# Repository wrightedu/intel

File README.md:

# Welcome!

## Today we are meeting in: 152C Russ for our FINAL DAY!!!

Great job on your designs all!  We will recume fabrication after lunch if anyone has any loose ends to tie up on their boards.

Resources:

* This site: [**github.com/wrightedu/intel**](github.com/wrightedu/intel)
  * [`./arduino-src/`](arduino-src/README.md) : arduino source files will be put here
  * [`./KiCad/`](KiCad/README.md) : KiCad example project files (mostly starter templates)
  * More folders and files will be added as we go through the course

* Download and install Arduino IDE from here: https://www.arduino.cc/en/software
* Download and install KiCAD from here: https://www.kicad.org/download/
* CSE Department Discord server: [https://discord.gg/pMUMzTt](https://discord.gg/pMUMzTt)
  * `#other-roles` and click on `Intel Summer Camp`

---

# The Format

* `*.md` a markdown formatted file for pretty web rendering here
* PowerPoint (`*.pptx`) and `*.pdf` files (self explanatory)
* `*.ino` files are for the arduino

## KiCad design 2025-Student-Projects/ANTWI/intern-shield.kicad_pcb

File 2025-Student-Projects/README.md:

# 2025 Student Projects

This folder contains the projects developed by the 20205 Intel Interns at Wright State University.

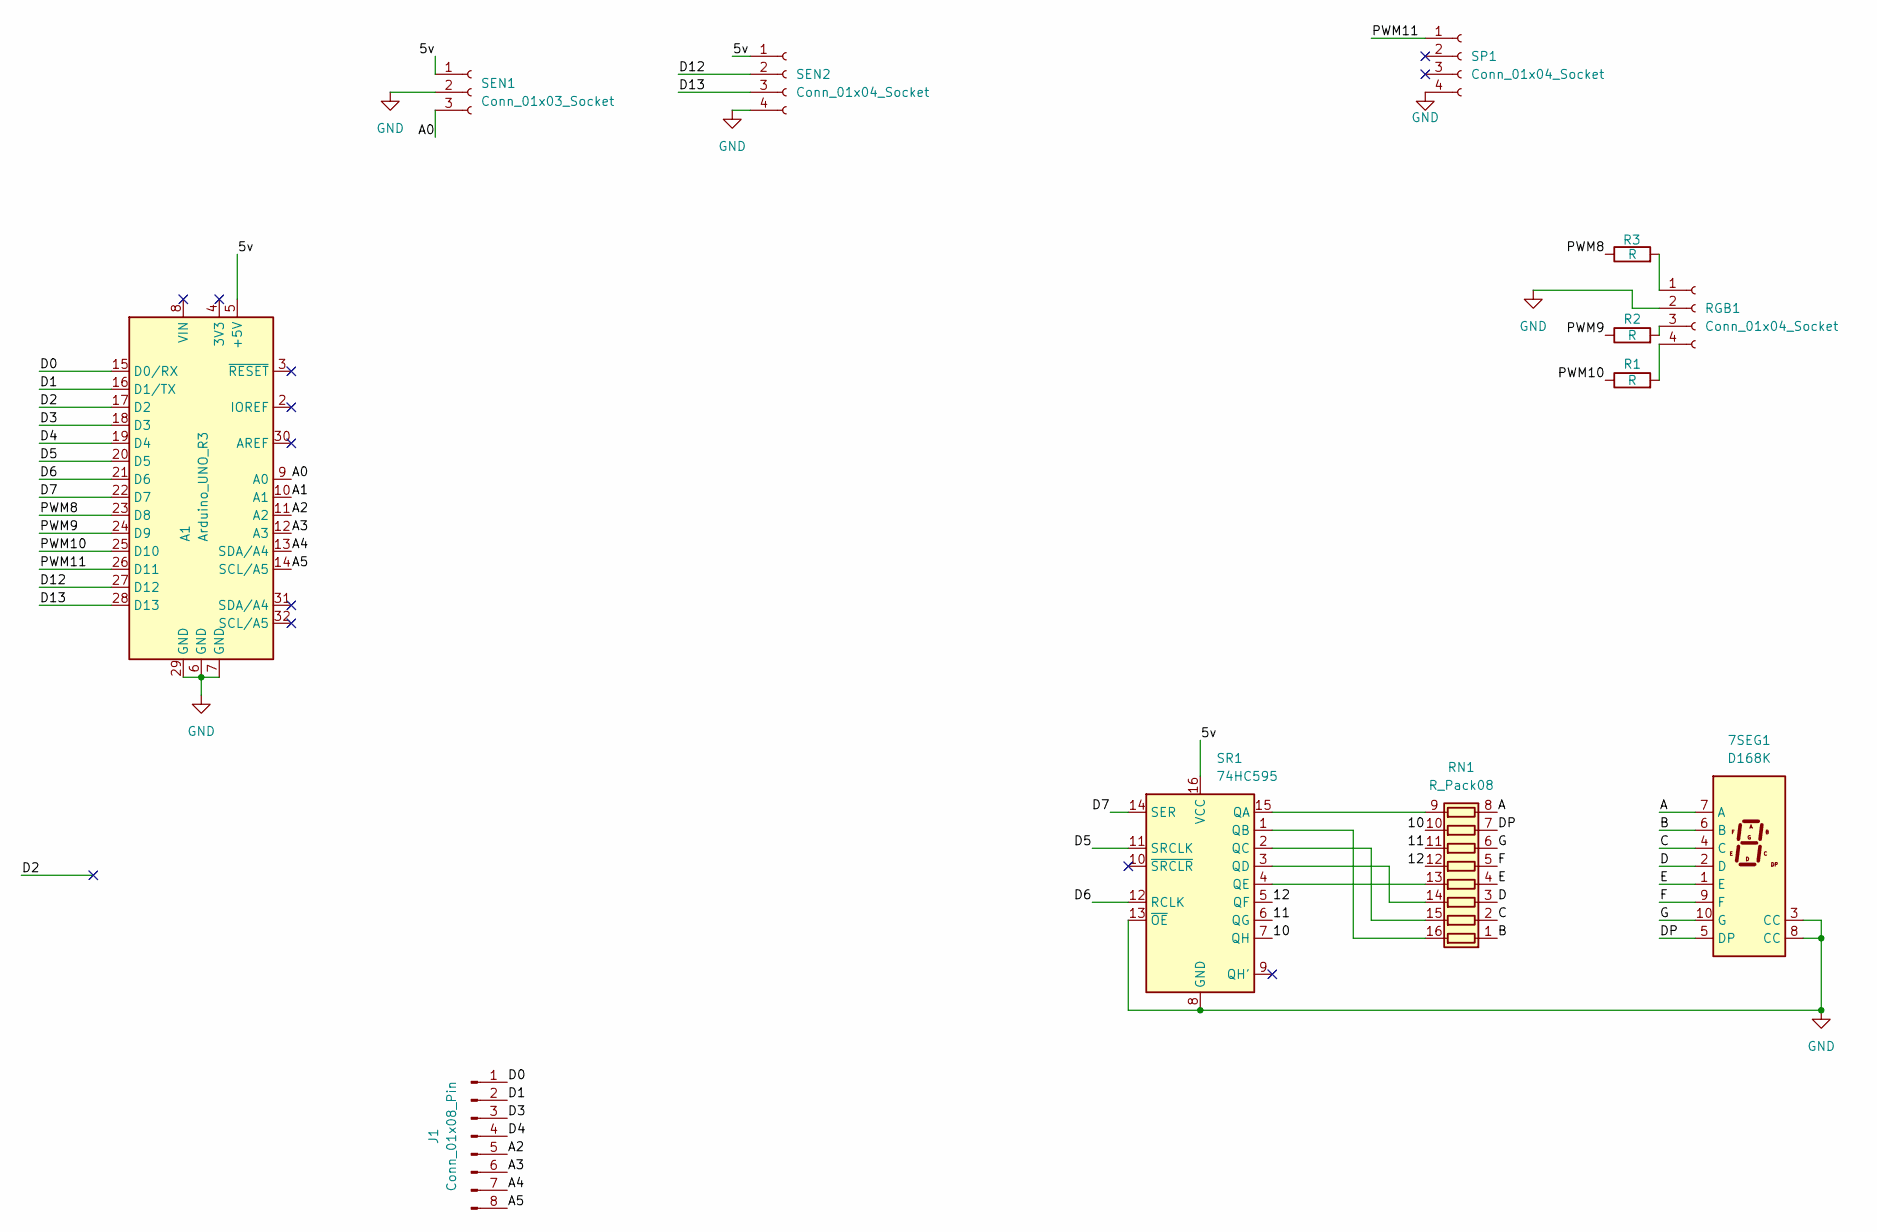
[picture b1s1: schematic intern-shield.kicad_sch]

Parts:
7SEG1: D168K; LS-5161AS
A1: Arduino_UNO_R3
J1: Conn_01x08_Pin; PinHeader_1x08_P2.54mm_Vertical
R1, R2, R3: R; R_Axial_DIN0207_L6.3mm_D2.5mm_P7.62mm_Horizontal
RGB1: Conn_01x04_Socket; PinSocket_1x04_P2.54mm_Vertical
RN1: R_Pack08; DIP-16_W7.62mm_Socket
SEN1: Conn_01x03_Socket; PinSocket_1x03_P2.54mm_Vertical
SEN2: Conn_01x04_Socket; PinSocket_1x04_P2.54mm_Vertical
SP1: Conn_01x04_Socket; PinSocket_1x04_P2.54mm_Vertical
SR1: 74HC595; DIP-16_W7.62mm_Socket

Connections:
/5v: A1.5 (+5V), SEN1.1, SEN2.1, SR1.16 (VCC)
/10: RN1.10 (R7.2), SR1.7 (QH)
/11: RN1.11 (R6.2), SR1.6 (QG)
/12: RN1.12 (R5.2), SR1.5 (QF)
/A: 7SEG1.7 (A), RN1.8 (R8.1)
/A0: A1.9 (A0), SEN1.3
/A1: A1.10 (A1)
/A2: A1.11 (A2), J1.5
/A3: A1.12 (A3), J1.6
/A4: A1.13 (SDA/A4), J1.7
/A5: A1.14 (SCL/A5), J1.8
/B: 7SEG1.6 (B), RN1.1 (R1.1)
/C: 7SEG1.4 (C), RN1.2 (R2.1)
/D: 7SEG1.2 (D), RN1.3 (R3.1)
/D0: A1.15 (D0/RX), J1.1
/D1: A1.16 (D1/TX), J1.2
/D2: A1.17 (D2)
/D3: A1.18 (D3), J1.3
/D4: A1.19 (D4), J1.4
/D5: A1.20 (D5), SR1.11 (SRCLK)
/D6: A1.21 (D6), SR1.12 (RCLK)
/D7: A1.22 (D7), SR1.14 (SER)
/D12: A1.27 (D12), SEN2.2
/D13: A1.28 (D13), SEN2.3
/DP: 7SEG1.5 (DP), RN1.7 (R7.1)
/E: 7SEG1.1 (E), RN1.4 (R4.1)
/F: 7SEG1.9 (F), RN1.5 (R5.1)
/G: 7SEG1.10 (G), RN1.6 (R6.1)
/PWM8: A1.23 (D8), R3.1
/PWM9: A1.24 (D9), R2.1
/PWM10: A1.25 (D10), R1.1
/PWM11: A1.26 (D11), SP1.1
GND: 7SEG1.3 (CC), 7SEG1.8 (CC), A1.6 (GND), A1.7 (GND), A1.29 (GND), RGB1.2, SEN1.2, SEN2.4, SP1.4, SR1.8 (GND), SR1.13 (~OE)
unnamed: R3.2, RGB1.1
unnamed: R2.2, RGB1.3
unnamed: R1.2, RGB1.4
unnamed: RN1.16 (R1.2), SR1.1 (QB)
unnamed: RN1.15 (R2.2), SR1.2 (QC)
unnamed: RN1.14 (R3.2), SR1.3 (QD)
unnamed: RN1.13 (R4.2), SR1.4 (QE)
unnamed: RN1.9 (R8.2), SR1.15 (QA)

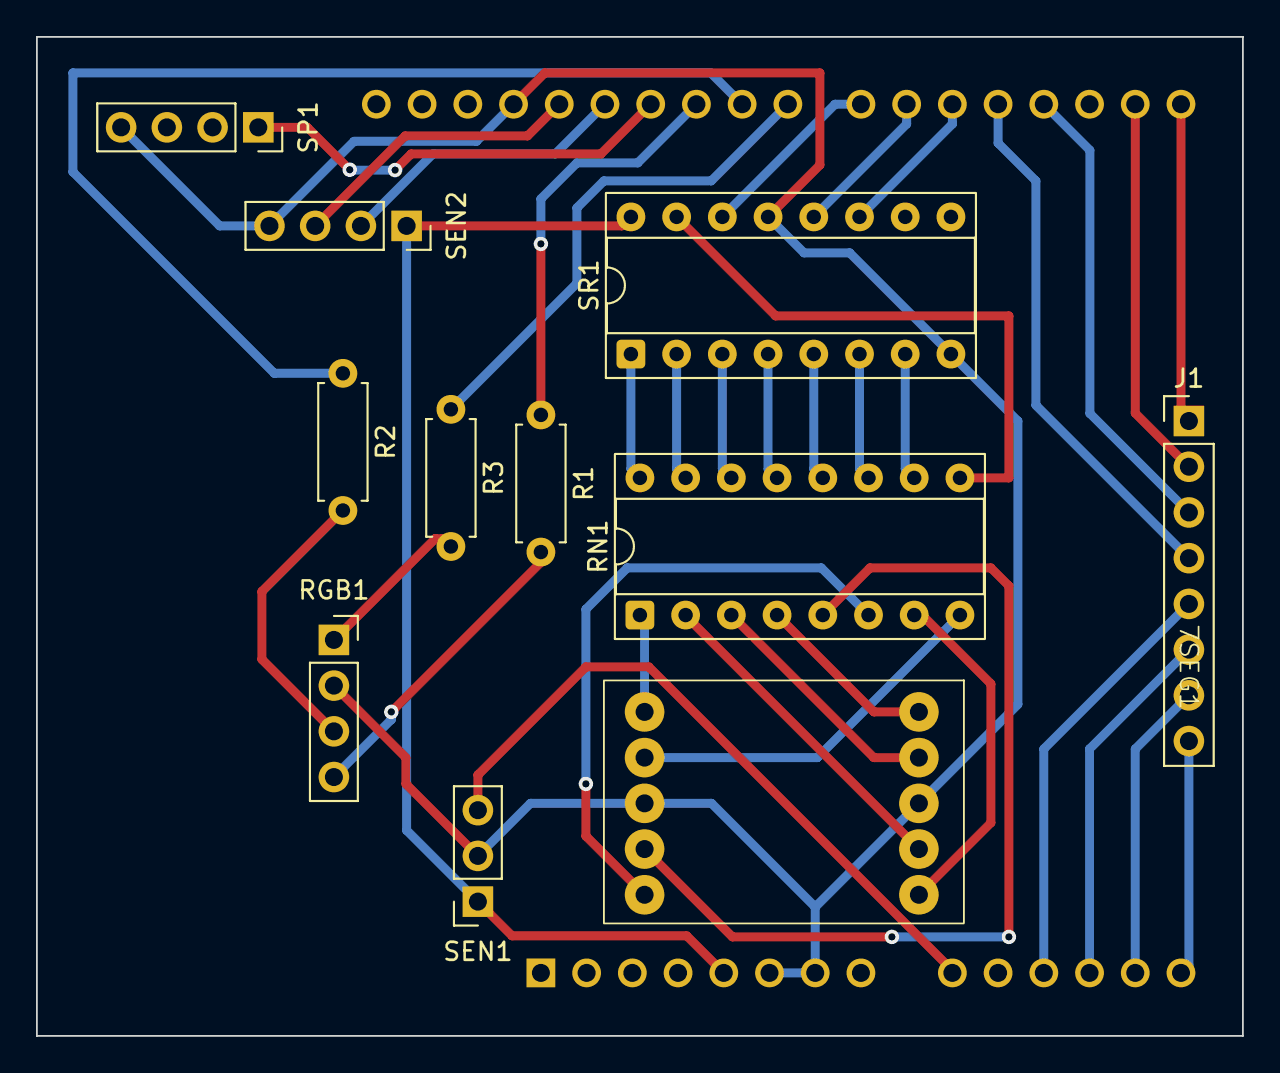
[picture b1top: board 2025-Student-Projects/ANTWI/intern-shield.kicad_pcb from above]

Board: 2 copper layers, 67.0 x 55.5 mm, 12 parts (1 on the bottom side), 39 nets.

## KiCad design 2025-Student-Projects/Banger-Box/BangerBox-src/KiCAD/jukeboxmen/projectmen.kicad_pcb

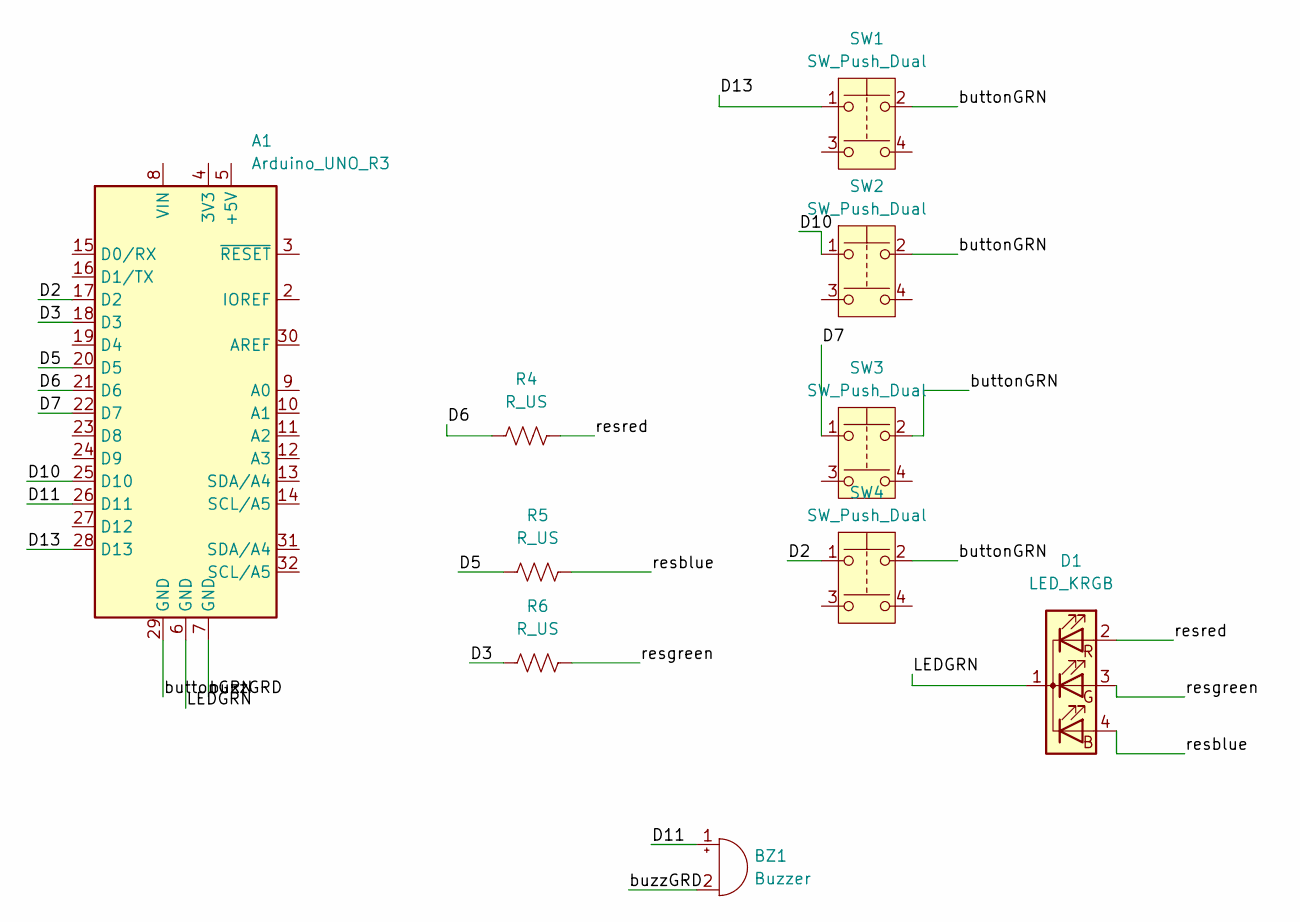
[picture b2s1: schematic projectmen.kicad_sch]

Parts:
A1: Arduino_UNO_R3
BZ1: Buzzer; Buzzer_12x9.5RM7.6
D1: LED_KRGB; LED_D5.0mm-4_RGB
R4, R5, R6: R_US; R_Axial_DIN0207_L6.3mm_D2.5mm_P10.16mm_Horizontal
SW1, SW2, SW3, SW4: SW_Push_Dual; SW_PUSH_6mm_H4.3mm

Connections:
/D2: A1.17 (D2), SW4.1
/D3: A1.18 (D3), R6.1
/D5: A1.20 (D5), R5.1
/D6: A1.21 (D6), R4.1
/D7: A1.22 (D7), SW3.1
/D10: A1.25 (D10), SW2.1
/D11: A1.26 (D11), BZ1.1 (+)
/D13: A1.28 (D13), SW1.1
/LEDGRN: A1.6 (GND), D1.1 (K)
/buttonGRN: A1.29 (GND), SW1.2, SW2.2, SW3.2, SW4.2
/buzzGRD: A1.7 (GND), BZ1.2 (-)
/resblue: D1.4 (BA), R5.2
/resgreen: D1.3 (GA), R6.2
/resred: D1.2 (RA), R4.2

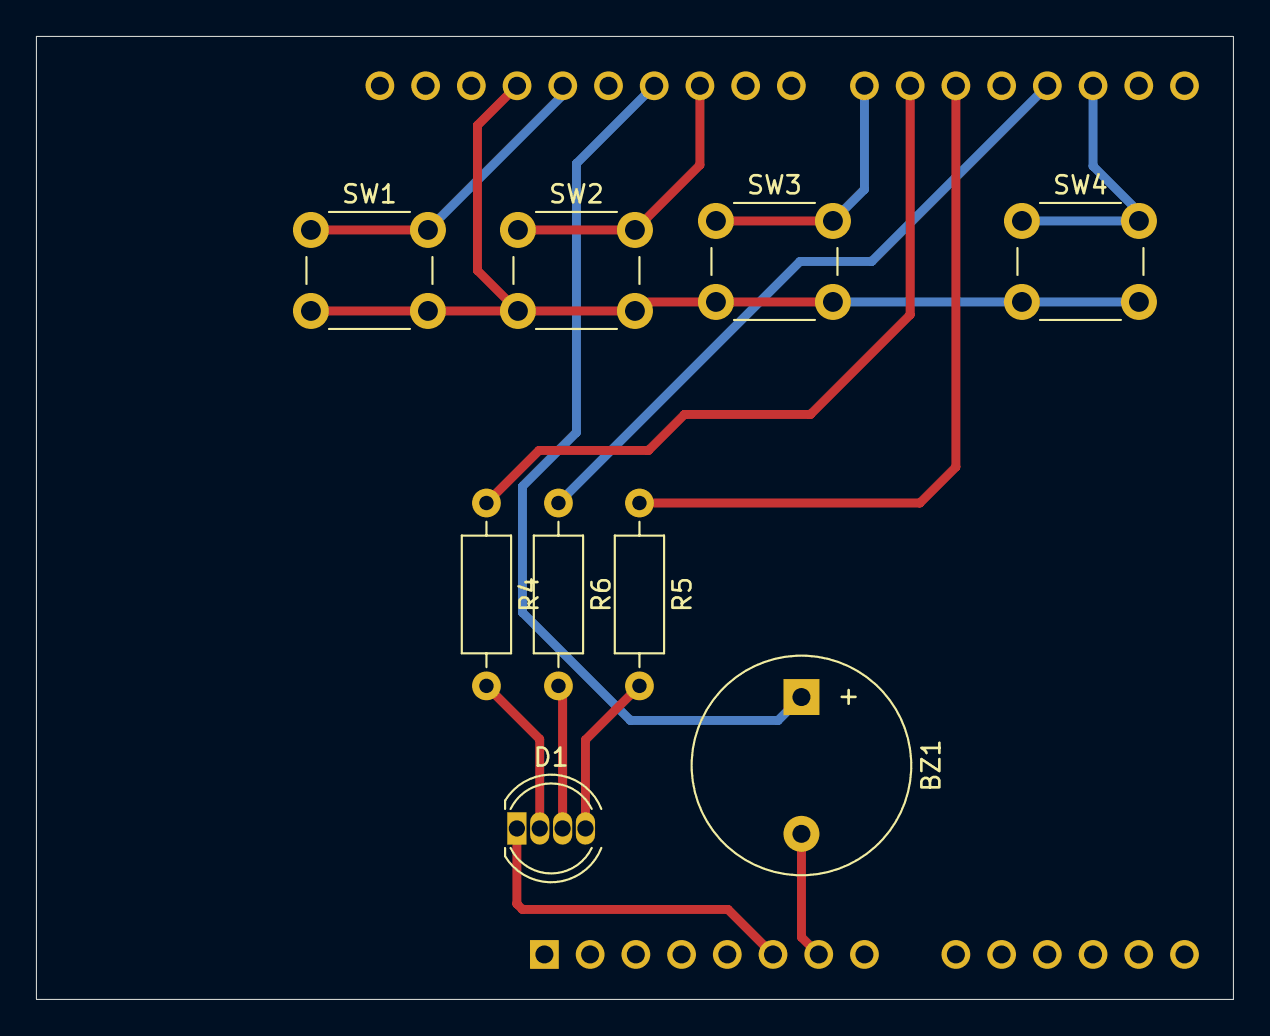
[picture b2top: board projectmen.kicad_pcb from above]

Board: 2 copper layers, 66.5 x 53.5 mm, 10 parts (1 on the bottom side), 14 nets.

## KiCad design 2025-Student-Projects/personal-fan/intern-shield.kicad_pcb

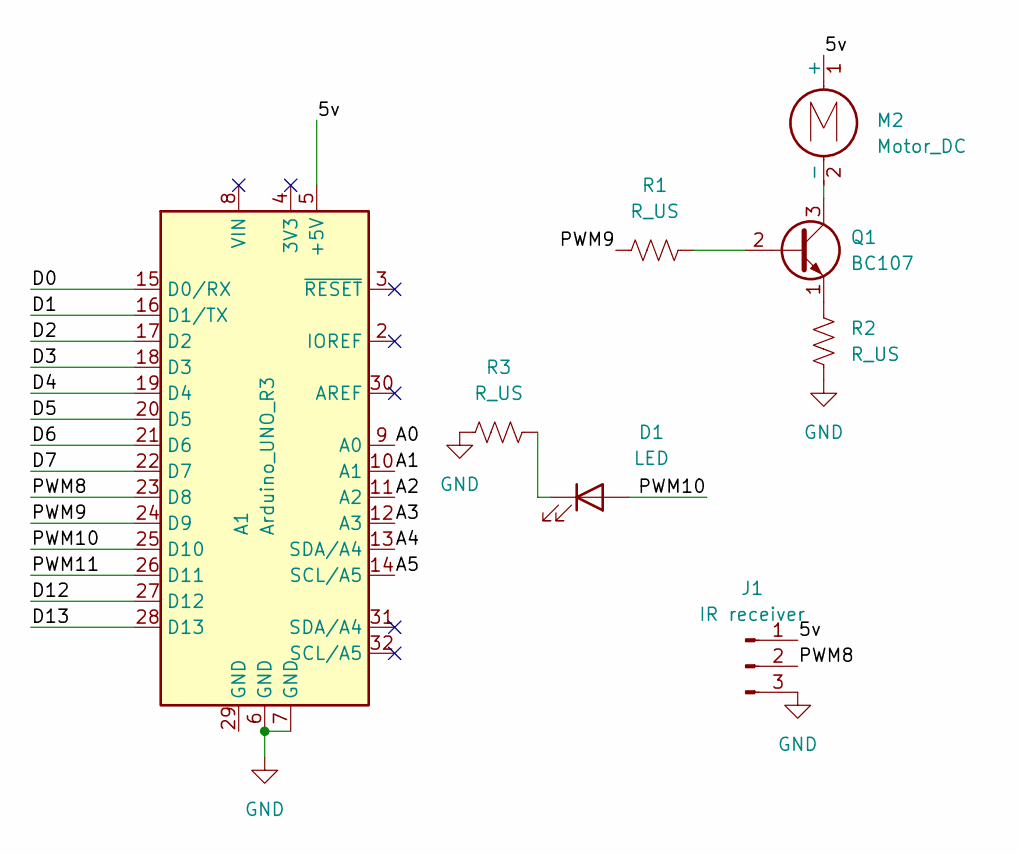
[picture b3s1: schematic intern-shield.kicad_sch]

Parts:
A1: Arduino_UNO_R3
D1: LED; LED_D3.0mm_Horizontal_O3.81mm_Z2.0mm
J1: IR receiver; PinHeader_1x03_P2.54mm_Vertical
M2: Motor_DC; PinHeader_1x02_P2.54mm_Vertical
Q1: BC107; TO-18-3
R1, R2, R3: R_US; R_Axial_DIN0207_L6.3mm_D2.5mm_P10.16mm_Horizontal

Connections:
/5v: A1.5 (+5V), J1.1, M2.1 (+)
/A0: A1.9 (A0)
/A1: A1.10 (A1)
/A2: A1.11 (A2)
/A3: A1.12 (A3)
/A4: A1.13 (SDA/A4)
/A5: A1.14 (SCL/A5)
/D0: A1.15 (D0/RX)
/D1: A1.16 (D1/TX)
/D2: A1.17 (D2)
/D3: A1.18 (D3)
/D4: A1.19 (D4)
/D5: A1.20 (D5)
/D6: A1.21 (D6)
/D7: A1.22 (D7)
/D12: A1.27 (D12)
/D13: A1.28 (D13)
/PWM8: A1.23 (D8), J1.2
/PWM9: A1.24 (D9), R1.1
/PWM10: A1.25 (D10), D1.2 (A)
/PWM11: A1.26 (D11)
GND: A1.6 (GND), A1.7 (GND), J1.3, R2.1, R3.1
unnamed: D1.1 (K), R3.2
unnamed: M2.2 (-), Q1.3 (C)
unnamed: Q1.2 (B), R1.2
unnamed: Q1.1 (E), R2.2

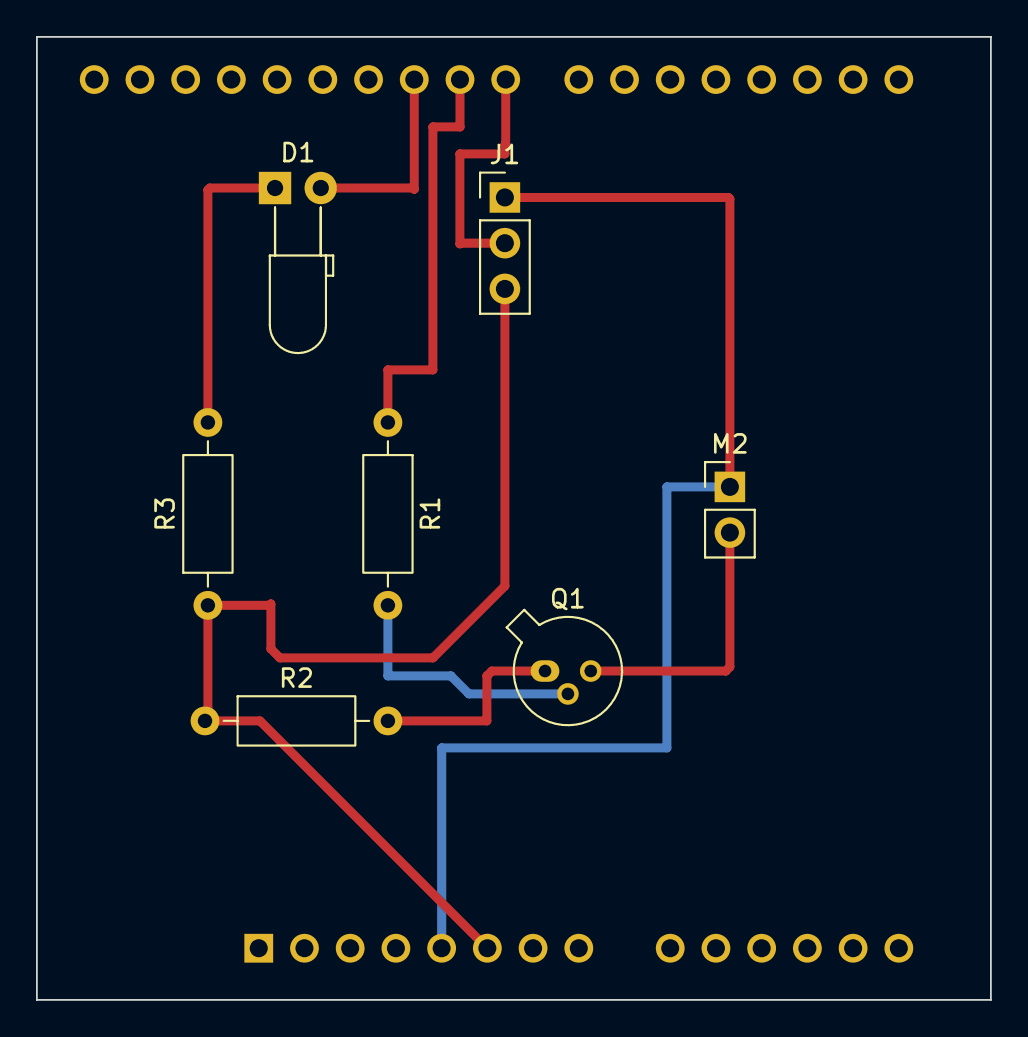
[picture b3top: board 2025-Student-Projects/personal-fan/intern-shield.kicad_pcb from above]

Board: 2 copper layers, 53.0 x 53.5 mm, 8 parts (1 on the bottom side), 9 nets.

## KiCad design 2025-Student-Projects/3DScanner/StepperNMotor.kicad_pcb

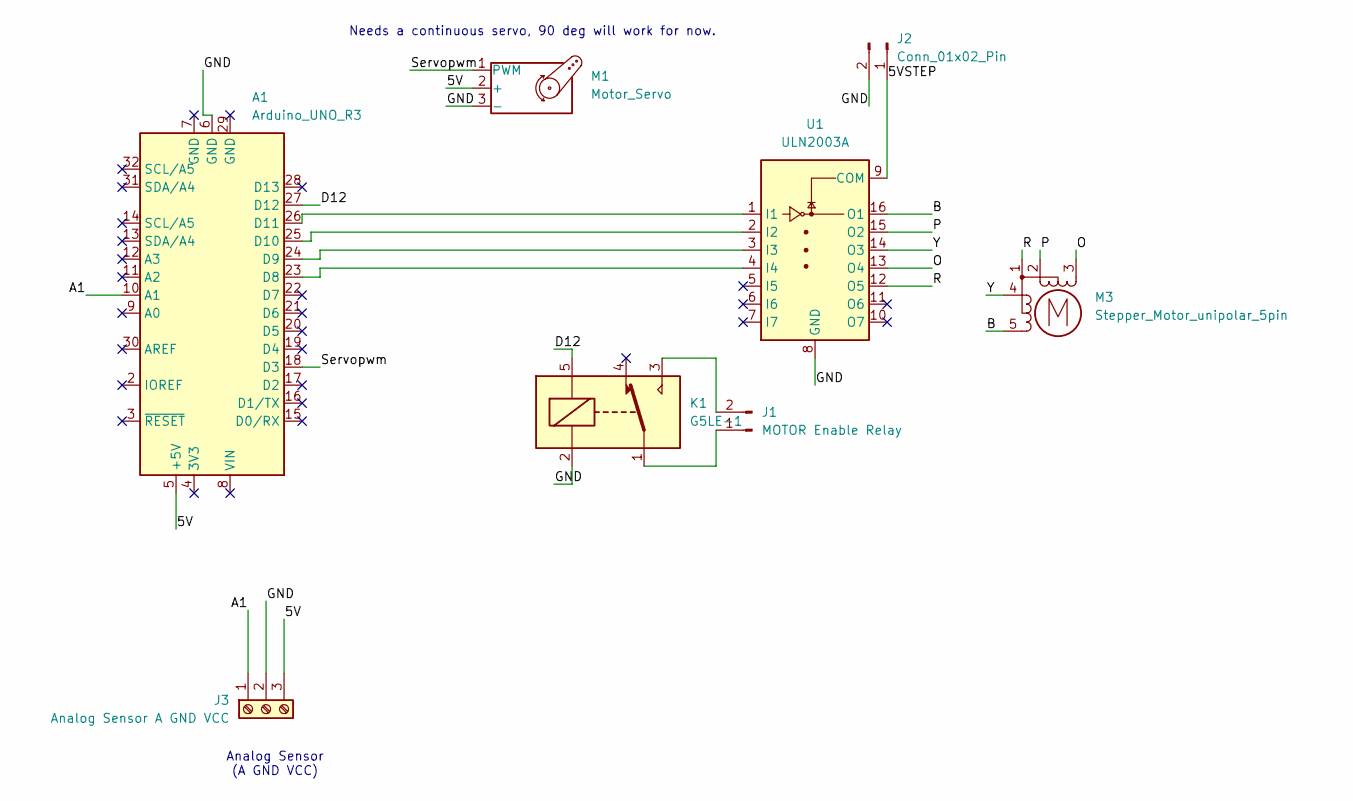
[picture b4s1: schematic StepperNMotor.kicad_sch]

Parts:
A1: Arduino_UNO_R3
J1: MOTOR Enable Relay; AMASS_XT30U-F_1x02_P5.0mm_Vertical
J2: Conn_01x02_Pin; PinSocket_1x02_P2.54mm_Vertical
J3: Analog Sensor A GND VCC; TerminalBlock_MetzConnect_Type055_RT01503HDWU_1x03_P5.00mm_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
K1: G5LE-1; Relay_SPDT_Omron-G5LE-1
M1: Motor_Servo; PinSocket_1x03_P2.54mm_Vertical
M3: Stepper_Motor_unipolar_5pin; PinHeader_1x05_P2.54mm_Vertical
U1: ULN2003A; DIP-16_W7.62mm

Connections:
/5V: A1.5 (+5V), J3.3, M1.2 (+)
/5VSTEP: J2.1, U1.9 (COM)
/A1: A1.10 (A1), J3.1
/B: M3.5, U1.16 (O1)
/D12: A1.27 (D12), K1.5
/GND: A1.6 (GND), J2.2, J3.2, K1.2, M1.3 (-), U1.8 (GND)
/O: M3.3 (-), U1.13 (O4)
/P: M3.2, U1.15 (O2)
/R: M3.1, U1.12 (O5)
/Servopwm: A1.18 (D3), M1.1 (PWM)
/Y: M3.4, U1.14 (O3)
unnamed: A1.23 (D8), U1.4 (I4)
unnamed: A1.24 (D9), U1.3 (I3)
unnamed: A1.25 (D10), U1.2 (I2)
unnamed: A1.26 (D11), U1.1 (I1)
unnamed: J1.1, K1.1
unnamed: J1.2, K1.3

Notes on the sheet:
Needs a continuous servo, 90 deg will work for now.
Analog Sensor (A GND VCC)

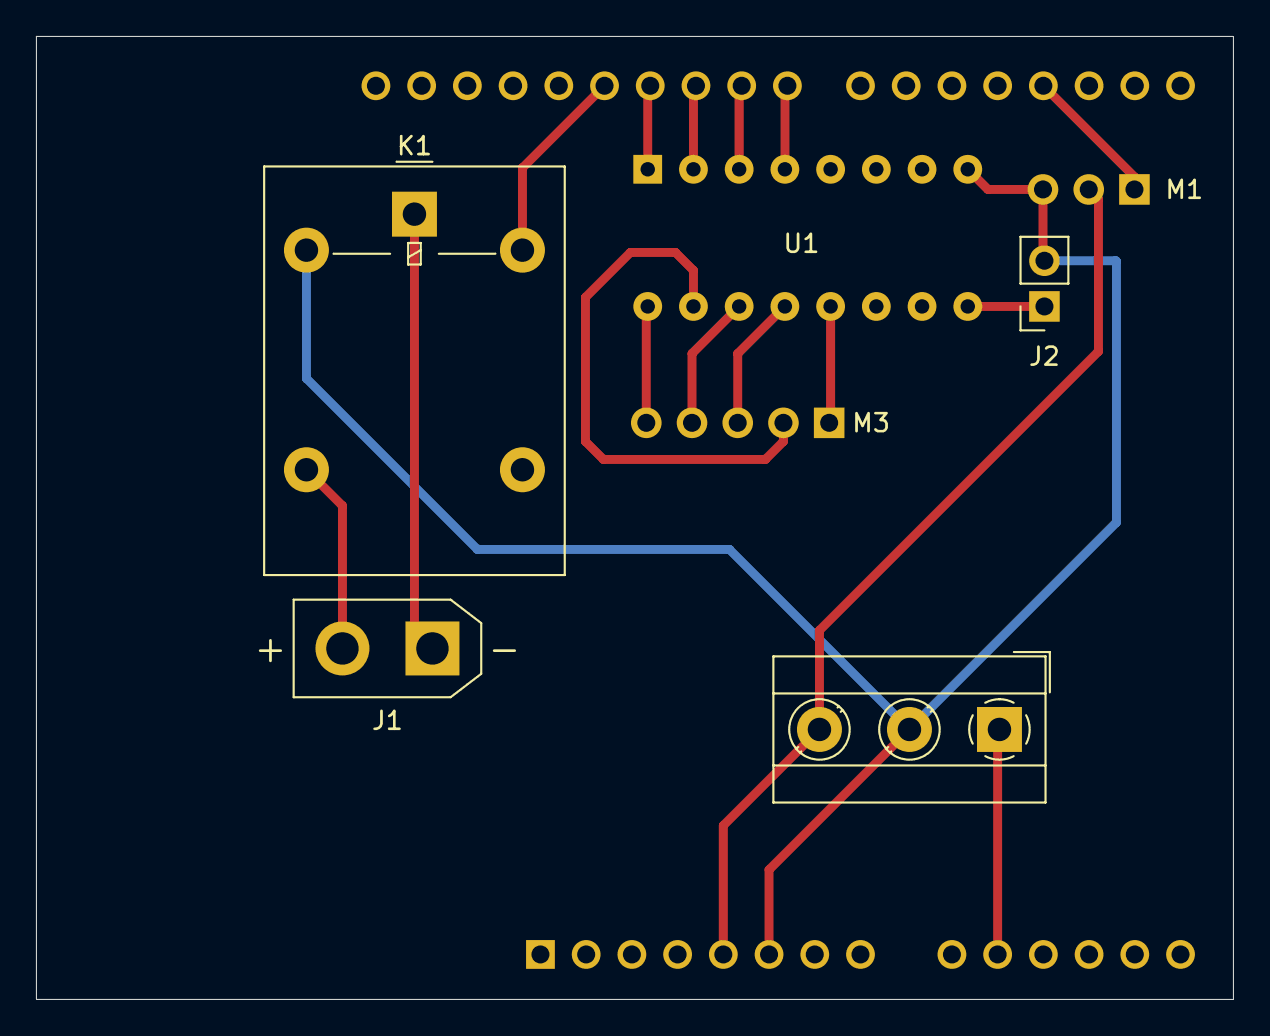
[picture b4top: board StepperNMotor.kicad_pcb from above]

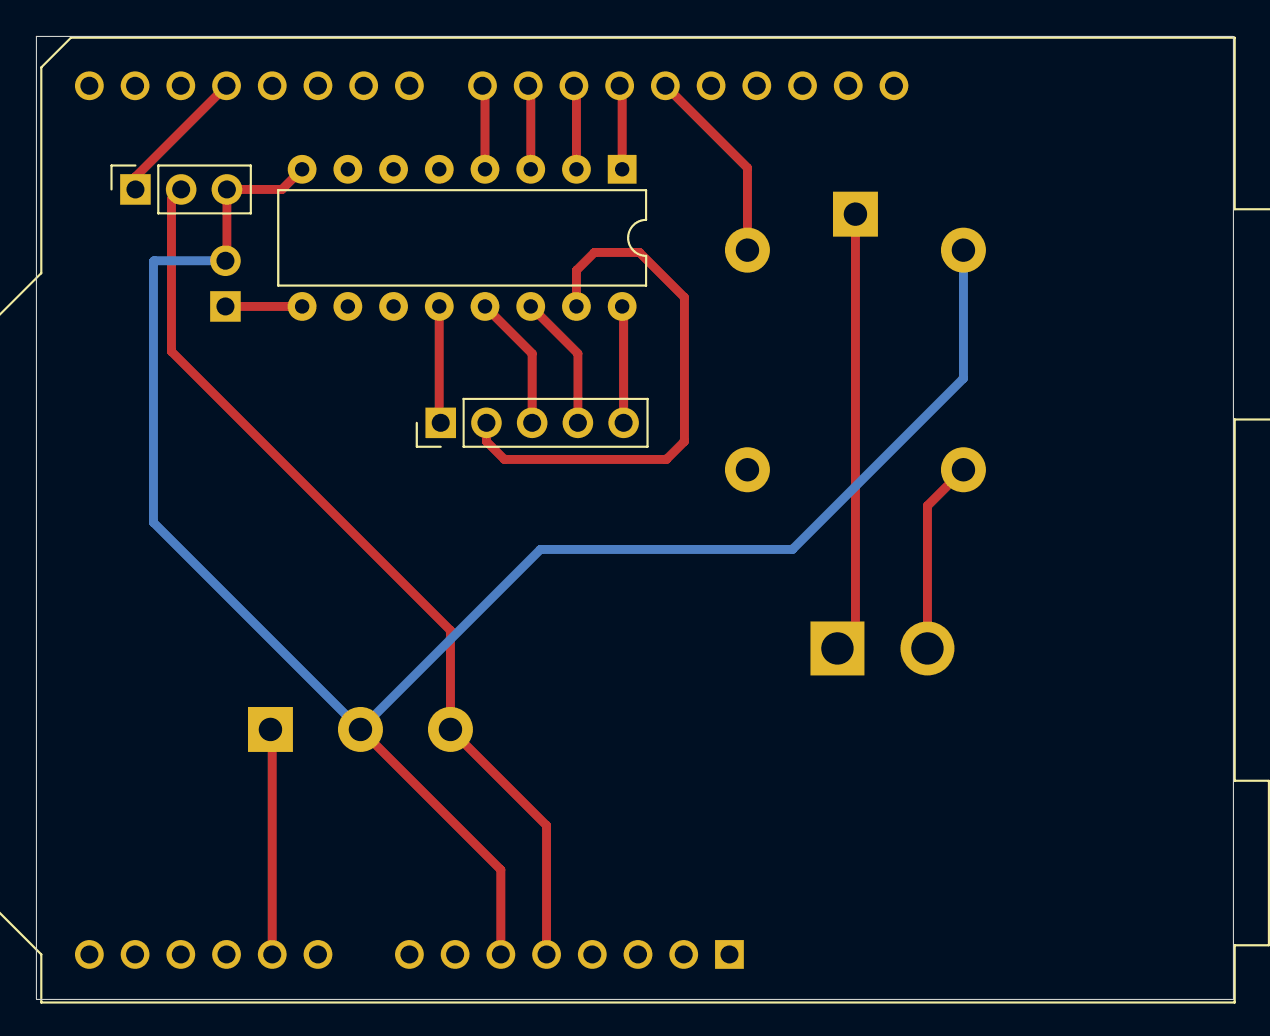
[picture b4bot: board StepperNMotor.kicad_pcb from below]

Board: 2 copper layers, 66.5 x 53.5 mm, 8 parts (4 on the bottom side), 17 nets.

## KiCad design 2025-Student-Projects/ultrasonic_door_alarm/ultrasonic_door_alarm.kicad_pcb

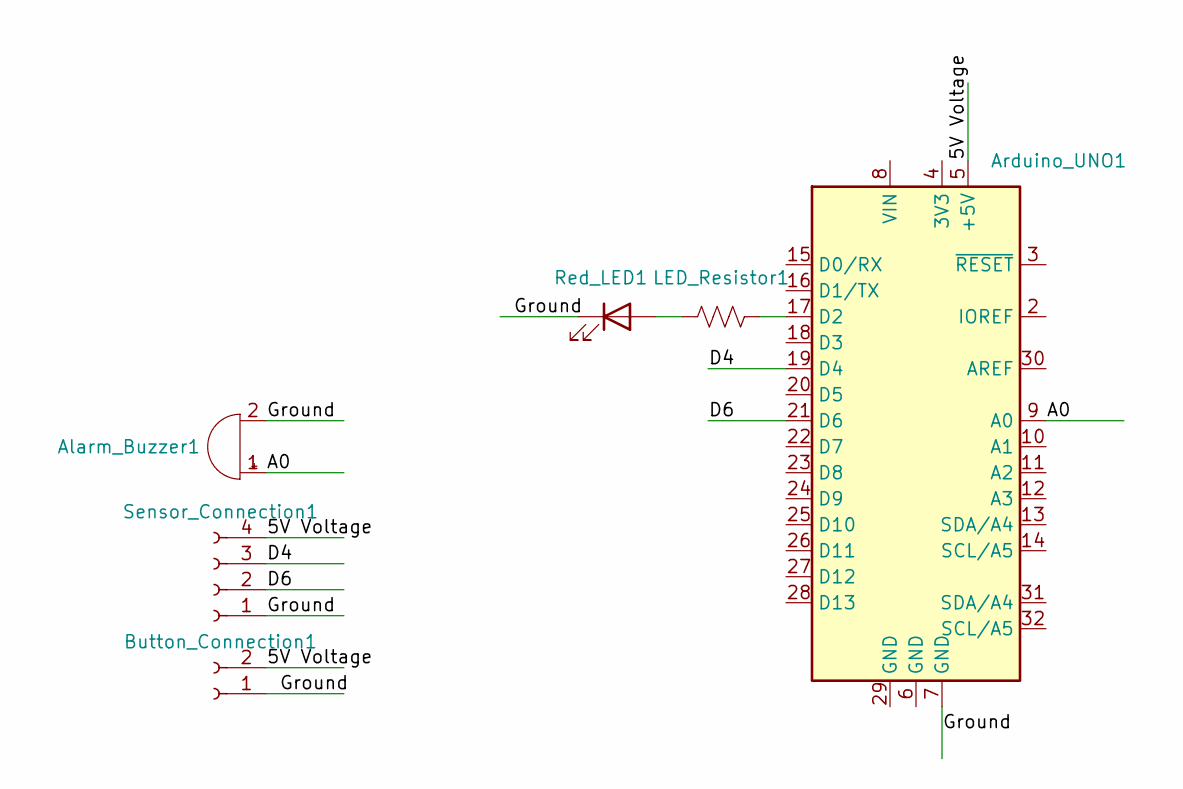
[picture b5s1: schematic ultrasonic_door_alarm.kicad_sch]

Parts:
Alarm_Buzzer1: Buzzer; Buzzer_12x9.5RM7.6
Arduino_UNO1: Arduino_UNO_R3
Button_Connection1: Conn_01x02_Socket; SW_PUSH_6mm_H4.3mm
LED_Resistor1: R_US; R_Axial_DIN0207_L6.3mm_D2.5mm_P10.16mm_Horizontal
Red_LED1: LED; LED_D5.0mm_Horizontal_O6.35mm_Z9.0mm
Sensor_Connection1: Conn_01x04_Socket; PinSocket_1x04_P2.54mm_Vertical

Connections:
/5V Voltage: Arduino_UNO1.5 (+5V), Button_Connection1.2, Sensor_Connection1.4
/A0: Alarm_Buzzer1.1 (+), Arduino_UNO1.9 (A0)
/D4: Arduino_UNO1.19 (D4), Sensor_Connection1.3
/D6: Arduino_UNO1.21 (D6), Sensor_Connection1.2
/Ground: Alarm_Buzzer1.2 (-), Arduino_UNO1.7 (GND), Button_Connection1.1, Red_LED1.1 (K), Sensor_Connection1.1
unnamed: Arduino_UNO1.17 (D2), LED_Resistor1.2
unnamed: LED_Resistor1.1, Red_LED1.2 (A)

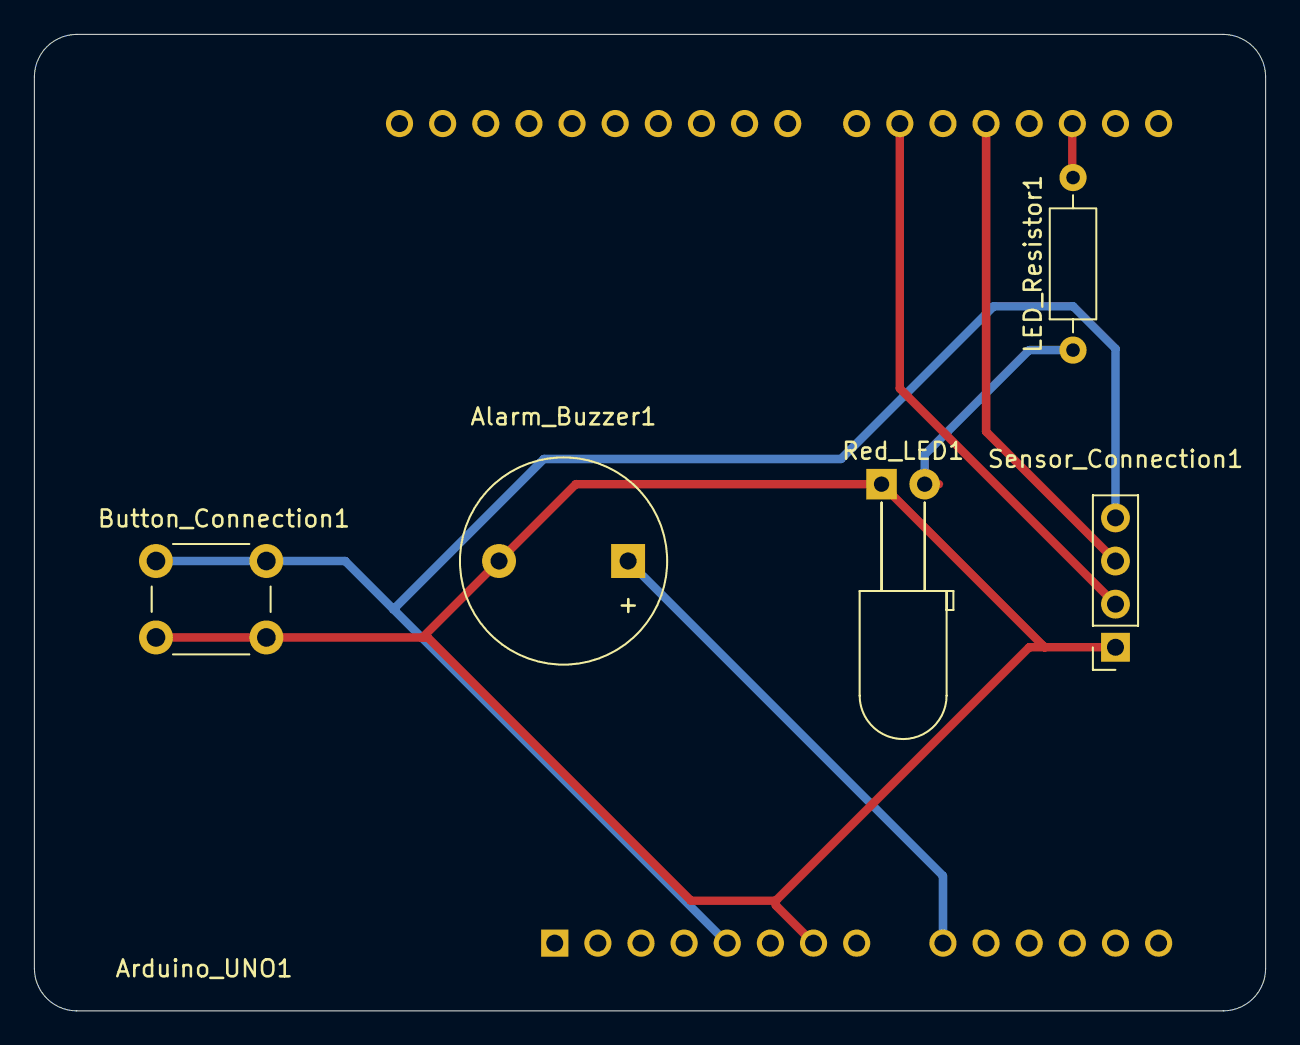
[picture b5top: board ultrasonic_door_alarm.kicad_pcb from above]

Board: 2 copper layers, 72.5 x 57.5 mm, 6 parts (1 on the bottom side), 7 nets.

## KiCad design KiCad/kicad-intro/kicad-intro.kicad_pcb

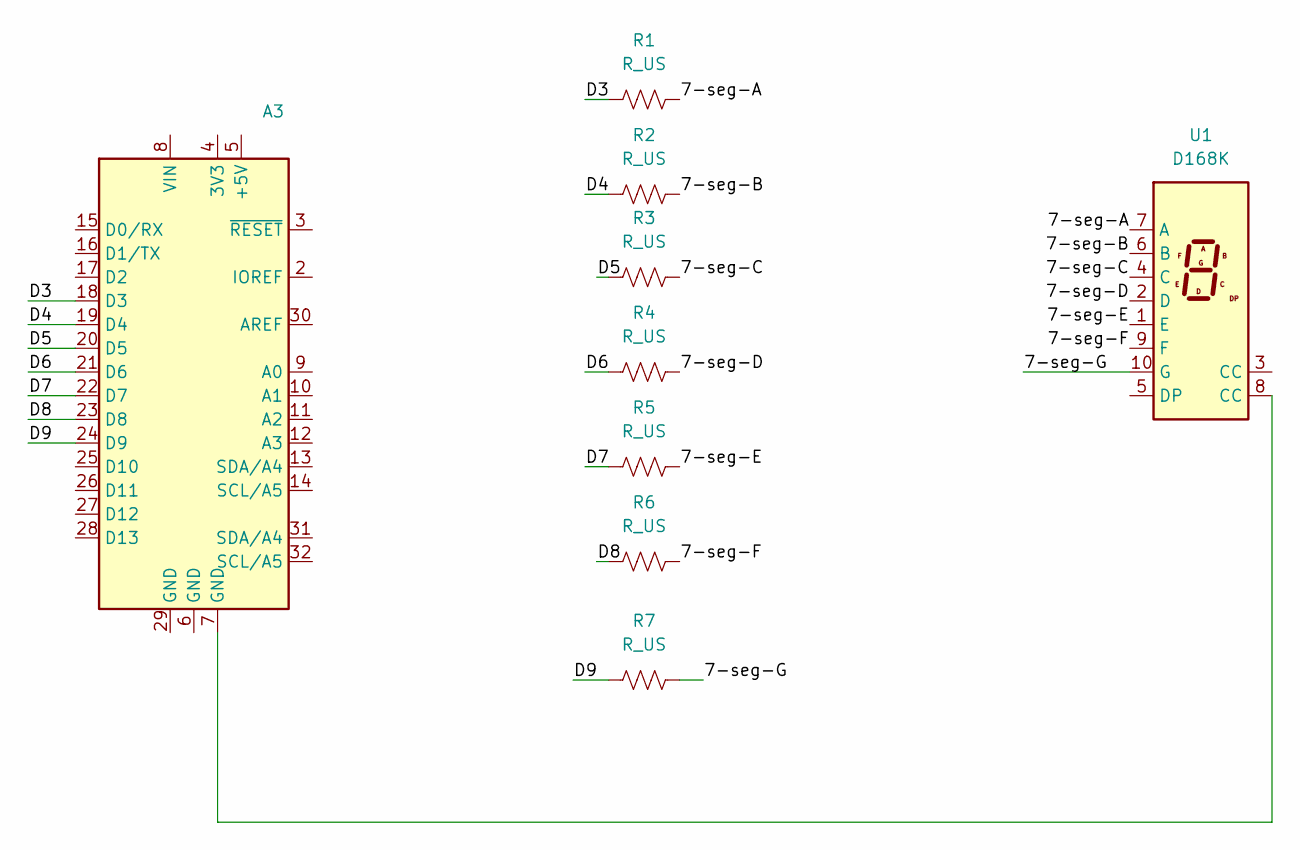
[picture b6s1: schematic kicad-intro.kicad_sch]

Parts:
A3: Arduino_UNO_R3
R1, R2, R3, R4, R5, R6, R7: R_US; R_Axial_DIN0207_L6.3mm_D2.5mm_P10.16mm_Horizontal
U1: D168K; D1X8K

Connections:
/7-seg-G: R7.2, U1.10 (G)
/D9: A3.24 (D9), R7.1
unnamed: A3.18 (D3), R1.1
unnamed: A3.19 (D4), R2.1
unnamed: A3.20 (D5), R3.1
unnamed: A3.21 (D6), R4.1
unnamed: A3.22 (D7), R5.1
unnamed: A3.23 (D8), R6.1
unnamed: A3.7 (GND), U1.8 (CC)
unnamed: R1.2, U1.7 (A)
unnamed: R2.2, U1.6 (B)
unnamed: R3.2, U1.4 (C)
unnamed: R4.2, U1.2 (D)
unnamed: R5.2, U1.1 (E)
unnamed: R6.2, U1.9 (F)

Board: 2 copper layers, 9 parts (0 on the bottom side), 15 nets, no tracks yet.

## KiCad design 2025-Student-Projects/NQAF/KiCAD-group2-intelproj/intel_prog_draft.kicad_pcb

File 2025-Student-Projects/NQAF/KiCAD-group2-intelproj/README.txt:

Designed By:

Serene Abdallah
Abigail Haut
Mariam Muhammad

Group 2

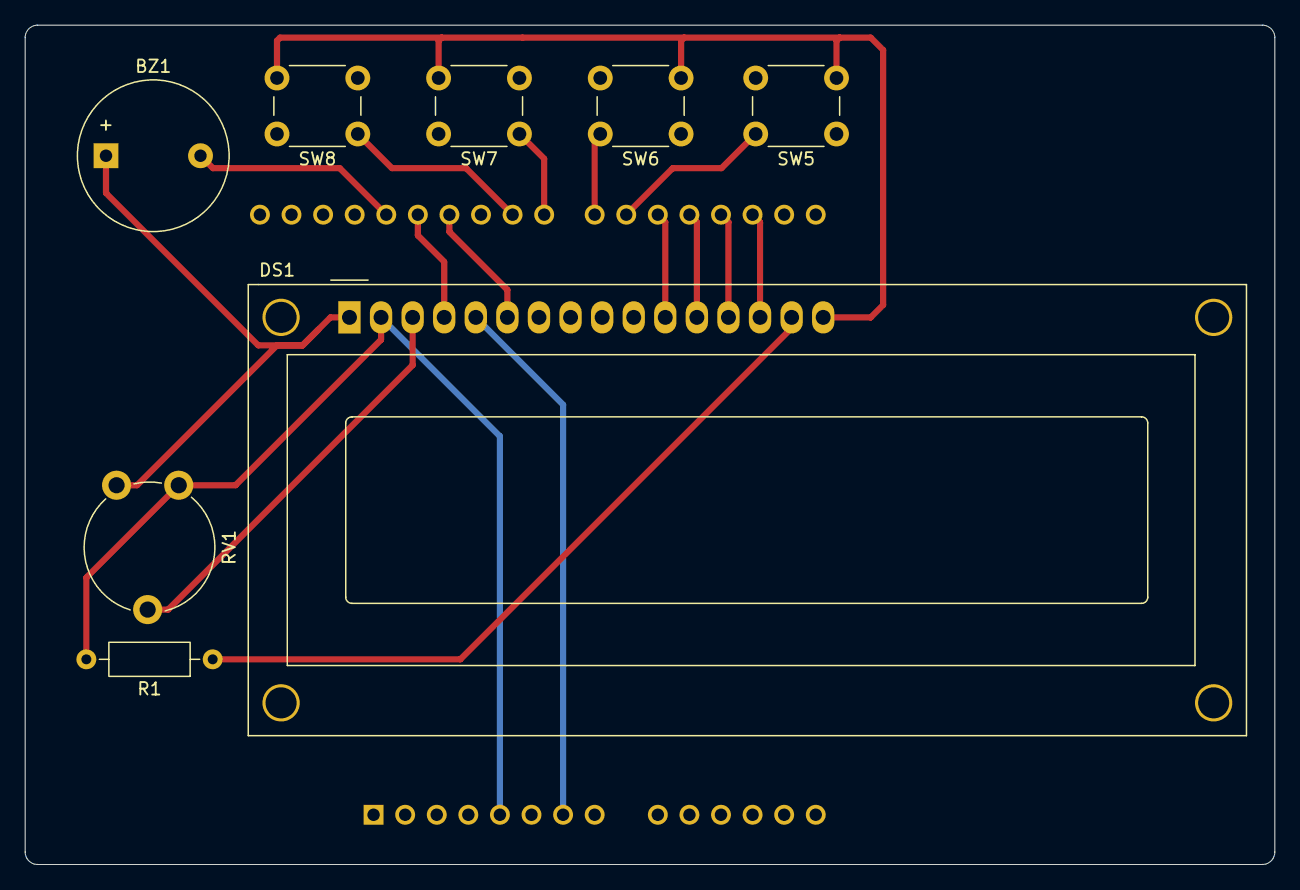
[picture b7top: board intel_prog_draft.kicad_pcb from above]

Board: 2 copper layers, 100.5 x 67.5 mm, 9 parts (1 on the bottom side), 15 nets.

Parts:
A1: Arduino_UNO_R3
BZ1: Buzzer; Buzzer_12x9.5RM7.6
DS1: WC1602A
R1: R_US; R_Axial_DIN0207_L6.3mm_D2.5mm_P10.16mm_Horizontal
RV1: R_Potentiometer; Potentiometer_Piher_PT-10-V10_Vertical
SW5, SW6, SW7, SW8: SW_Push; SW_PUSH_6mm

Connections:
/D2: A1.17 (D2), DS1.14 (D7)
/D3: A1.18 (D3), DS1.13 (D6)
/D4: A1.19 (D4), DS1.12 (D5)
/D5: A1.20 (D5), DS1.11 (D4)
/D6: A1.21 (D6), SW5.1
/D7: A1.22 (D7), SW6.1
/D8: A1.23 (D8), SW7.1
/D9: A1.24 (D9), SW8.1
/D11: A1.26 (D11), DS1.6 (E)
/D12: A1.27 (D12), DS1.4 (RS)
/D13: A1.28 (D13), BZ1.2 (-)
/Vdd: A1.5 (+5V), DS1.2 (VDD), R1.2, RV1.3
/Vss: A1.7 (GND), BZ1.1 (+), DS1.1 (VSS), DS1.5 (R/W), DS1.16 (LED(-)), RV1.1, SW5.2, SW6.2, SW7.2, SW8.2
unnamed: DS1.15 (LED(+)), R1.1
unnamed: DS1.3 (VO), RV1.2

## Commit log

2024-07-01 init
    needs lots more work but a first draft
2024-07-02 init code
2024-07-02 init
2024-07-02 fixing things
2024-07-02 discord sever link
2024-07-02 fix links
2024-07-02 number, not num
2024-07-02 commit messages are important (I guess)
2024-07-03 kicad project tweaks
2024-07-03 zipping files
2024-07-03 gerring tired of fixing spelling ettots
2024-07-08 resistors, footprints, and org
2024-07-08 cleanup
2024-07-08 move and fix
2024-07-08 footprint lib
2024-07-08 BUM, da-DUM, DUm, dum, zip it real good
2024-07-14 working rgb and 7-segment blink
2024-07-15 Created programs (most work)
2024-07-22 Updated programs and documentation
2025-07-01 add tail chasing to countdown
2025-07-01 Add JoshBoard schematic
2025-07-01 add joshyboard that probably stil works
2025-07-01 welcome slides added
2025-07-01 Fix joshypoo's typo
2025-07-08 Added BDike folder of student project
2025-07-24 Banger Box Arduino code
2025-07-25 trying to resolve conflicts...
2025-07-25 Update TNMT.h
    IT WORKS NOW
2025-07-25 lgtm
2025-07-25 TNMT should be TMNT...
